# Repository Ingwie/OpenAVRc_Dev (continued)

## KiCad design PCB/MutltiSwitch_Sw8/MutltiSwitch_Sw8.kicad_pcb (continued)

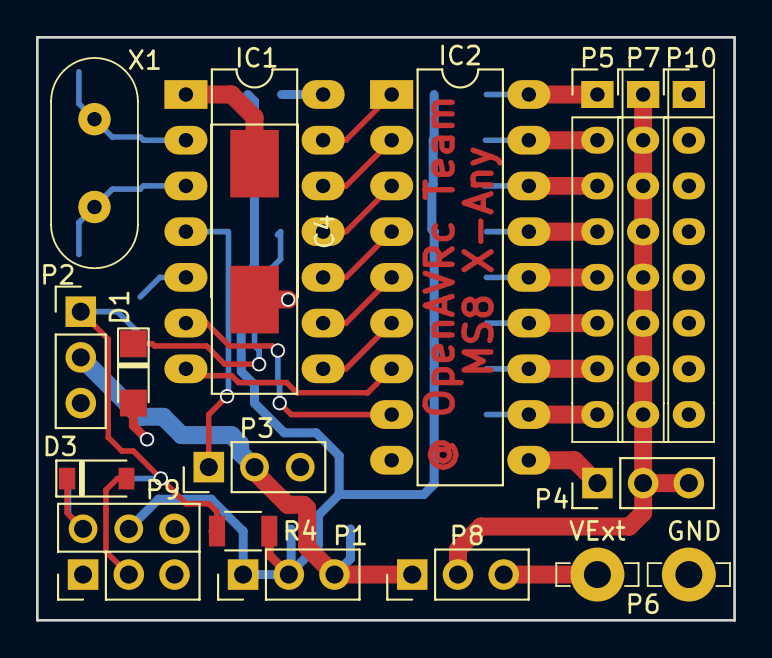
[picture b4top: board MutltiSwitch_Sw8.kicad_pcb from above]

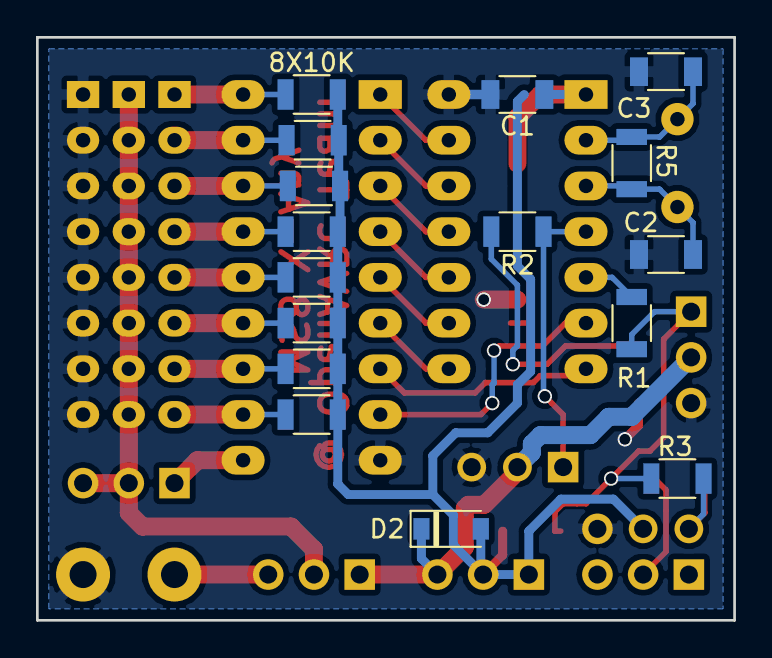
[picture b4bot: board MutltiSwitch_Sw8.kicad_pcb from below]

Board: 2 copper layers, 38.7 x 32.4 mm, 33 parts (16 on the bottom side), 30 nets.

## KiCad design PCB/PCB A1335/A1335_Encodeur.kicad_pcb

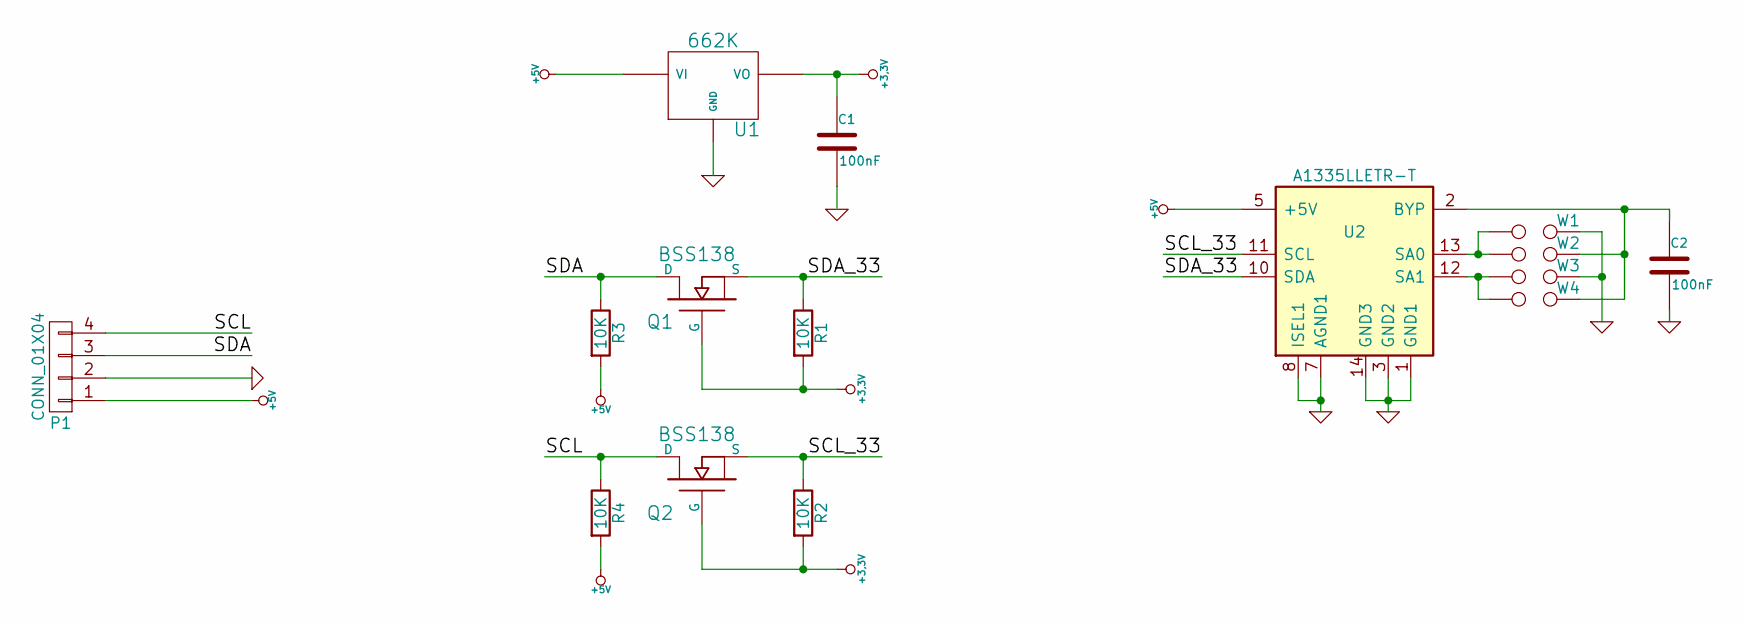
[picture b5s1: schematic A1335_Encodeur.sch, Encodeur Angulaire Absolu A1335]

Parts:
C1, C2: 100nF; C_0805
P1: CONN_01X04; SMD_1x04_Pitch2mm
Q1, Q2: BSS138; SOT-23_MOS_P
R1, R2, R3, R4: 10K; R_0805
U1: 662K; SOT-23
U2: A1335LLETR-T; TSSOP-14_4.4x5mm_Pitch0.65mm
W1, W2, W3, W4: 0; TESTPT

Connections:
+3.3V: C1.1, Q1.G, Q2.G, R1.2, R2.2, U1.2 (VO)
+5V: P1.1, R3.2, R4.2, U1.3 (VI), U2.5 (+5V)
/SCL: P1.4, Q2.D, R4.1
/SCL_33: Q2.S, R2.1, U2.11 (SCL)
/SDA: P1.3, Q1.D, R3.1
/SDA_33: Q1.S, R1.1, U2.10 (SDA)
GND: C1.2, C2.2, P1.2, U1.1 (GND), U2.1 (GND1), U2.3 (GND2), U2.7 (AGND1), U2.8 (ISEL1), U2.14 (GND3), W1.2, W3.2
unnamed: C2.1, U2.2 (BYP), W2.2, W4.2
unnamed: U2.12 (SA1), W3.1, W4.1
unnamed: U2.13 (SA0), W1.1, W2.1

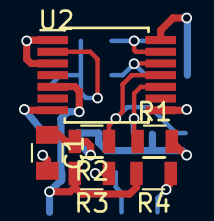
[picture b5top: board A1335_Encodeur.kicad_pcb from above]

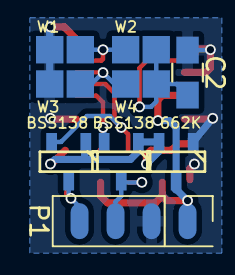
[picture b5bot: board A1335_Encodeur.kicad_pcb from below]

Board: 2 copper layers, 15 parts (9 on the bottom side), 10 nets.
